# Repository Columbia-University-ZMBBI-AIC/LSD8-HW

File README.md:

# LSD8-HW
LED Synchronous Driver Hardware

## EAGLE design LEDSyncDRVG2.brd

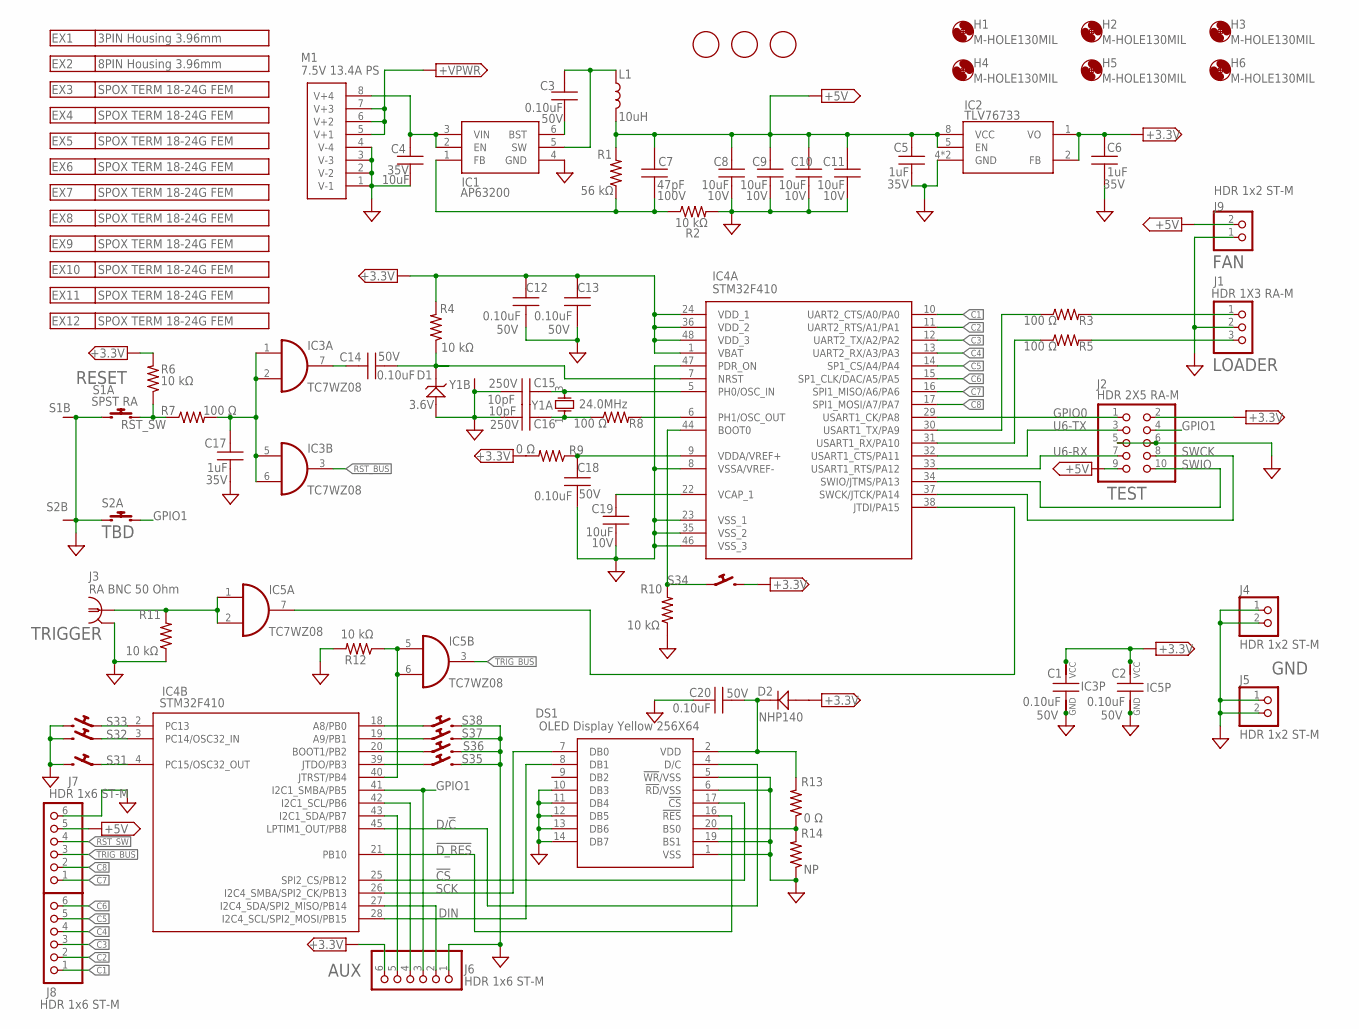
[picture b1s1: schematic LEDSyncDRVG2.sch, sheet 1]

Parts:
C1, C2, C3, C12, C13, C14, C18, C20: 0.10uF; MLCC_0603
C4: 10uF; MLCC_1206
C5, C6, C17: 1uF; MLCC_0603
C7: 47pF; MLCC_0603
C8, C9, C10, C11, C19: 10uF; MLCC_0603
C15, C16: 10pF; MLCC_0603
D1: 3.6V; SOD3716X135N_DIODE
D2: NHP140; SOD-123FL
DS1: OLED Display Yellow 256X64; DISPLAY20P
H1, H2, H3, H4, H5, H6: M-HOLE130MIL; 4-40_130HOLE_260CLEAR
IC1: AP63200; SOT95P280X100-6N
IC2: TLV76733; VSSOP8-DGK-065P
IC3, IC5: TC7WZ08; SOP50P310X90-8N
IC4: STM32F410; QFP50P900X900X160-48N
J1: HDR 1X3 RA-M; HDR_1X3RAS
J2: HDR 2X5 RA-M; HDR_2X5M_RAS
J3: RA BNC 50 Ohm; BNC_AMP_227161
J4, J5, J9: HDR 1x2 ST-M; HDR_1X2
J6: HDR 1x6 ST-M; HDR_1X06
J7, J8: HDR 1x6 ST-M; HDR_1X06; MPN NP
L1: 10uH; IND_5X5MM-5045
M1: 7.5V 13.4A PS; PS_5X3_MOLEX8P
R1: 56 kΩ; R0603
R2, R4, R6, R10, R11, R12: 10 kΩ; R0603
R3, R5, R7, R8: 100 Ω; R0603
R9, R13: 0 Ω; R0603
R14: NP; R0603
S1, S2: SPST RA; SITCH_PB_RA_800SP9B6M6RE
S3: DIP8-RA; SWITCHX8_DIP_RA_0.1IN
U$1, U$2, U$3: FIDUCIAL; FIDUCIAL_1MM
Y1: 24.0MHz; XTAL4P_3.2X2.5MM

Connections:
!CS: DS1.17 (!CS), IC4.25 (SPI2_CS/PB12)
!D_RES: DS1.16 (!RES), IC4.21 (PB10)
+3.3V: C1.2, C2.2, C6.1, C12.2, C13.2, D2.2 (A), IC2.1 (VO), IC2.2 (FB), IC3.8 (VCC), IC4.1 (VBAT), IC4.24 (VDD_1), IC4.36 (VDD_2), IC4.48 (VDD_3), IC5.8 (VCC), J2.2, J6.6, R4.2, R6.2, R9.2, S3.8; also elsewhere on the board
+5V: C5.1, C7.2, C8.2, C9.2, C10.2, C11.2, IC2.5 (EN), IC2.8 (VCC), J2.9, J7.5, J9.2, L1.2, R1.2; also elsewhere on the board
+VPWR: M1.5 (V+1), M1.6 (V+2), M1.7 (V+3); also elsewhere on the board
C1: IC4.10 (UART2_CTS/A0/PA0), J8.1; also elsewhere on the board
C2: IC4.11 (UART2_RTS/A1/PA1), J8.2; also elsewhere on the board
C3: IC4.12 (UART2_TX/A2/PA2), J8.3; also elsewhere on the board
C4: IC4.13 (UART2_RX/A3/PA3), J8.4; also elsewhere on the board
C5: IC4.14 (SP1_CS/A4/PA4), J8.5; also elsewhere on the board
C6: IC4.15 (SP1_CLK/DAC/A5/PA5), J8.6; also elsewhere on the board
C7: IC4.16 (SPI1_MISO/A6/PA6), J7.1; also elsewhere on the board
C8: IC4.17 (SPI1_MOSI/A7/PA7), J7.2; also elsewhere on the board
D/!C: DS1.4 (D/C), IC4.45 (LPTIM1_OUT/PB8)
DIN: DS1.8 (DB1), IC4.28 (I2C4_SCL/SPI2_MOSI/PB15)
GND: C1.1, C2.1, C4.2, C5.2, C6.2, C8.1, C9.1, C10.1, C11.1, C12.1, C13.1, C15.1, C16.1, C17.2, C18.1, C19.1, C20.2, D1.2 (A), DS1.1 (VSS), DS1.5 (!WR!/VSS), DS1.6 (!RD!/VSS), DS1.10 (DB3), DS1.11 (DB4), DS1.12 (DB5), DS1.13 (DB6), DS1.14 (DB7), DS1.19 (BS1), IC1.4 (GND), IC2.4 (GND), IC2.6 (GND), IC3.4 (GND), IC4.8 (VSSA/VREF-), IC4.23 (VSS_1), IC4.35 (VSS_2), IC4.46 (VSS_3), IC4.47 (PDR_ON), IC5.4 (GND), J1.2, J2.5, J2.6, J3.2, J4.1, J4.2, J5.1, J5.2, J6.1, J7.6, J9.1, M1.1 (V-1), M1.2 (V-2), M1.3 (V-3), M1.4 (V-4), R2.2, R10.1, R11.1, R12.2, R14.1, S1.1, S1.MH1 (G1), S1.MH2 (G1), S2.1, S2.MH1 (G1), S2.MH2 (G1), S3.2, S3.4, S3.6, S3.10, S3.12, S3.14, S3.16, Y1.2 (G1), Y1.4 (G1); also elsewhere on the board
GPIO0: IC4.29 (USART1_CK/PA8), J2.1
GPIO1: IC4.41 (I2C1_SMBA/PB5), J2.4, J6.3, S2.3
unnamed: C4.1, IC1.2 (EN), IC1.3 (VIN), M1.8 (V+4)
unnamed: IC4.6 (PH1/OSC_OUT), R8.2
unnamed: C16.2, R8.1, Y1.1 (IO)
unnamed: C15.2, IC4.5 (PH0/OSC_IN), Y1.3 (OI)
unnamed: C18.2, IC4.9 (VDDA/VREF+), R9.1
unnamed: IC4.3 (PC14/OSC32_IN), S3.3
unnamed: C19.2, IC4.22 (VCAP_1)
unnamed: IC4.44 (BOOT0), R10.2, S3.7
unnamed: C14.1, D1.1 (K), IC4.7 (NRST), R4.1
unnamed: C3.2, IC1.5 (SW), L1.1
unnamed: C7.1, IC1.1 (FB), R1.1, R2.1
unnamed: C3.1, IC1.6 (BST)
unnamed: IC4.18 (A8/PB0), S3.15
unnamed: IC4.19 (A9/PB1), S3.13
unnamed: J1.3, R5.2
unnamed: J1.1, R3.2
unnamed: IC4.20 (BOOT1/PB2), S3.11
unnamed: IC4.39 (JTDO/PB3), S3.9
unnamed: IC4.2 (PC13), S3.5
unnamed: DS1.20 (BS0), R13.1, R14.2
unnamed: IC4.4 (PC15/OSC32_OUT), S3.1
unnamed: IC4.38 (JTDI/PA15), IC5.7 (O)
unnamed: C20.1, D2.1 (K), DS1.2 (VDD), R13.2
unnamed: IC4.27 (I2C4_SDA/SPI2_MISO/PB14), J6.2
unnamed: IC4.30 (USART1_TX/PA9), R3.1
unnamed: IC4.43 (I2C1_SDA/PB7), J6.5
unnamed: IC4.42 (I2C1_SCL/PB6), J6.4
unnamed: C14.2, IC3.7 (O)
unnamed: IC4.31 (USART1_RX/PA10), R5.1
unnamed: IC4.40 (JTRST/PB4), IC5.5 (I0), IC5.6 (I1), R12.1
unnamed: IC5.1 (I0), IC5.2 (I1), J3.1, R11.2
RST: C17.1, IC3.1 (I0), IC3.2 (I1), IC3.5 (I0), IC3.6 (I1), R7.2
RST_BUS: IC3.3 (O); also elsewhere on the board
RST_SW: J7.4, R6.1, R7.1, S1.3
SCK: DS1.7 (DB0), IC4.26 (I2C4_SMBA/SPI2_CK/PB13)
SWCK: IC4.37 (SWCK/JTCK/PA14), J2.8
SWIO: IC4.34 (SWIO/JTMS/PA13), J2.10
TRIG_BUS: IC5.3 (O), J7.3; also elsewhere on the board
U6-RX: IC4.33 (USART1_RTS/PA12), J2.7
U6-TX: IC4.32 (USART1_CTS/PA11), J2.3

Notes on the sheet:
TEST
AUX
LOADER
TRIGGER
GND
RESET
TBD
FAN

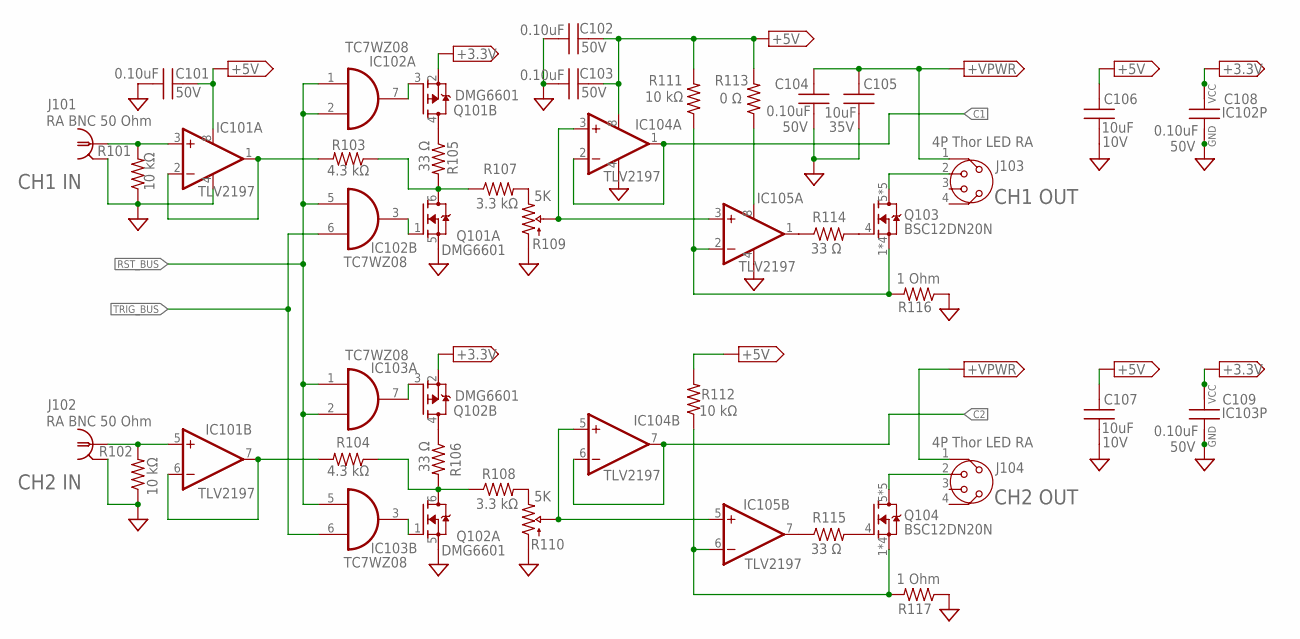
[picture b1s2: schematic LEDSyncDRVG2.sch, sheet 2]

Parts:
C101, C102, C103, C104, C108, C109: 0.10uF; MLCC_0603
C105: 10uF; MLCC_1206
C106, C107: 10uF; MLCC_0603
IC101, IC104, IC105: TLV2197; VSSOP8-DGK-065P
IC102, IC103: TC7WZ08; SOP50P310X90-8N
J101, J102: RA BNC 50 Ohm; BNC_AMP_227161
J103, J104: 4P Thor LED RA; CIR_PHX4P_RA
Q101, Q102: DMG6601; SOT95P280X100-6N
Q103, Q104: BSC12DN20N; TDSON-8
R101, R102, R111, R112: 10 kΩ; R0603
R103, R104: 4.3 kΩ; R0603
R105, R106, R114, R115: 33 Ω; R0603
R107, R108: 3.3 kΩ; R0603
R109, R110: 5K; MTBOURNS_RA_LONG
R113: 0 Ω; R0603
R116, R117: 1 Ohm; R1225

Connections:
+3.3V: C108.2, C109.2, IC102.8 (VCC), IC103.8 (VCC), Q101.2 (S), Q102.2 (S); also elsewhere on the board
+5V: C101.2, C102.2, C103.2, C106.2, C107.2, IC101.8 (V+), IC104.8 (V+), R111.2, R112.2, R113.2; also elsewhere on the board
+VPWR: C104.2, C105.1, J103.1, J104.1; also elsewhere on the board
C1: IC104.1 (OUT), IC104.2 (-IN); also elsewhere on the board
C2: IC104.6 (-IN), IC104.7 (OUT); also elsewhere on the board
GND: C101.1, C102.1, C103.1, C104.1, C105.2, C106.1, C107.1, C108.1, C109.1, IC101.4 (V-), IC102.4 (GND), IC103.4 (GND), IC104.4 (V-), IC105.4 (V-), J101.2, J102.2, Q101.5 (S), Q102.5 (S), R101.1, R102.1, R109.1 (START), R110.1 (START), R116.1, R117.1; also elsewhere on the board
unnamed: Q102.4 (D), R106.1
unnamed: Q101.4 (D), R105.1
unnamed: Q101.6 (D), R103.1, R105.2, R107.1
unnamed: IC102.3 (O), Q101.1 (G)
unnamed: IC102.7 (O), Q101.3 (G)
unnamed: IC101.1 (OUT), IC101.2 (-IN), R103.2
unnamed: IC101.3 (+IN), J101.1, R101.2
unnamed: R107.2, R109.3 (END)
unnamed: Q102.6 (D), R104.1, R106.2, R108.1
unnamed: IC104.3 (+IN), IC105.3 (+IN), R109.2 (WIPER)
unnamed: IC105.1 (OUT), R114.1
unnamed: IC105.2 (-IN), Q103.1 (S), Q103.2 (S), Q103.3 (S), Q103.10 (S), R111.1, R116.2
unnamed: Q103.4 (G), R114.2
unnamed: IC103.3 (O), Q102.1 (G)
unnamed: J103.2, Q103.5 (D), Q103.6 (D), Q103.7 (D), Q103.8 (D), Q103.9 (D)
unnamed: IC103.7 (O), Q102.3 (G)
unnamed: IC101.5 (+IN), J102.1, R102.2
unnamed: IC101.6 (-IN), IC101.7 (OUT), R104.2
unnamed: R108.2, R110.3 (END)
unnamed: IC104.5 (+IN), IC105.5 (+IN), R110.2 (WIPER)
unnamed: IC105.6 (-IN), Q104.1 (S), Q104.2 (S), Q104.3 (S), Q104.10 (S), R112.1, R117.2
unnamed: IC105.7 (OUT), R115.1
unnamed: Q104.4 (G), R115.2
unnamed: J104.2, Q104.5 (D), Q104.6 (D), Q104.7 (D), Q104.8 (D), Q104.9 (D)
unnamed: IC105.8 (V+), R113.1
RST_BUS: IC102.1 (I0), IC102.2 (I1), IC102.5 (I0), IC103.1 (I0), IC103.2 (I1), IC103.5 (I0); also elsewhere on the board
TRIG_BUS: IC102.6 (I1), IC103.6 (I1); also elsewhere on the board

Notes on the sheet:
CH1 IN
CH2 IN
CH1 OUT
CH2 OUT

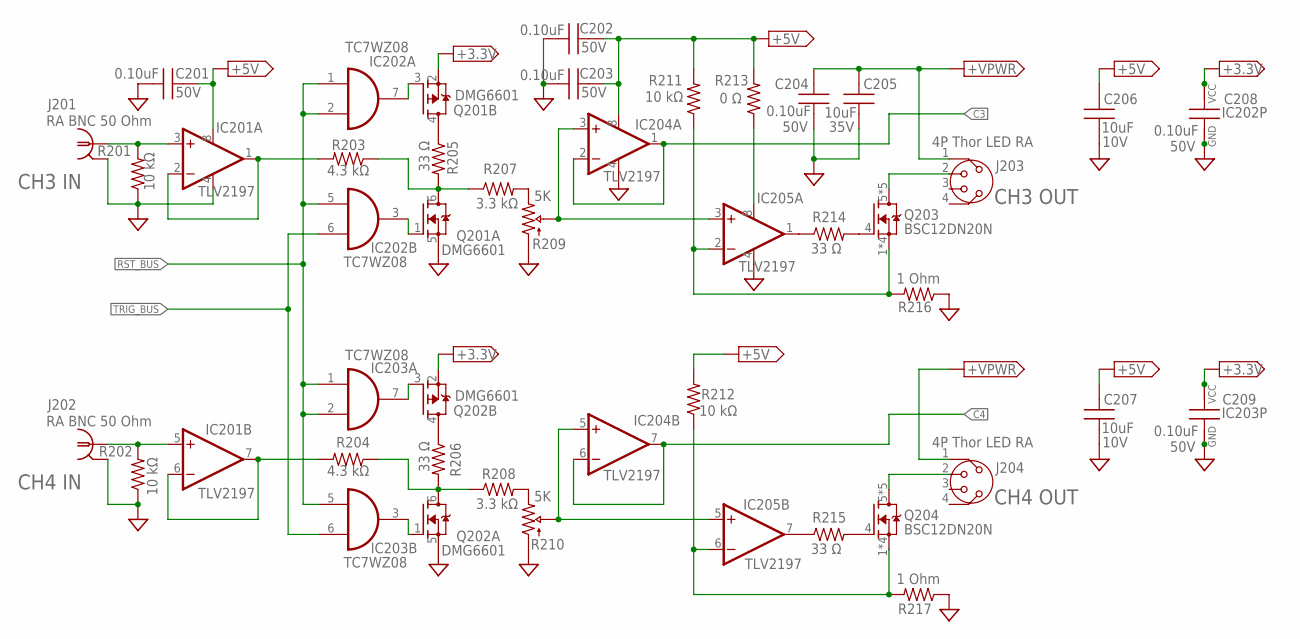
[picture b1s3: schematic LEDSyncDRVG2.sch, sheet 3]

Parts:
C201, C202, C203, C204, C208, C209: 0.10uF; MLCC_0603
C205: 10uF; MLCC_1206
C206, C207: 10uF; MLCC_0603
IC201, IC204, IC205: TLV2197; VSSOP8-DGK-065P
IC202, IC203: TC7WZ08; SOP50P310X90-8N
J201, J202: RA BNC 50 Ohm; BNC_AMP_227161
J203, J204: 4P Thor LED RA; CIR_PHX4P_RA
Q201, Q202: DMG6601; SOT95P280X100-6N
Q203, Q204: BSC12DN20N; TDSON-8
R201, R202, R211, R212: 10 kΩ; R0603
R203, R204: 4.3 kΩ; R0603
R205, R206, R214, R215: 33 Ω; R0603
R207, R208: 3.3 kΩ; R0603
R209, R210: 5K; MTBOURNS_RA_LONG
R213: 0 Ω; R0603
R216, R217: 1 Ohm; R1225

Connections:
+3.3V: C208.2, C209.2, IC202.8 (VCC), IC203.8 (VCC), Q201.2 (S), Q202.2 (S); also elsewhere on the board
+5V: C201.2, C202.2, C203.2, C206.2, C207.2, IC201.8 (V+), IC204.8 (V+), R211.2, R212.2, R213.2; also elsewhere on the board
+VPWR: C204.2, C205.1, J203.1, J204.1; also elsewhere on the board
C3: IC204.1 (OUT), IC204.2 (-IN); also elsewhere on the board
C4: IC204.6 (-IN), IC204.7 (OUT); also elsewhere on the board
GND: C201.1, C202.1, C203.1, C204.1, C205.2, C206.1, C207.1, C208.1, C209.1, IC201.4 (V-), IC202.4 (GND), IC203.4 (GND), IC204.4 (V-), IC205.4 (V-), J201.2, J202.2, Q201.5 (S), Q202.5 (S), R201.1, R202.1, R209.1 (START), R210.1 (START), R216.1, R217.1; also elsewhere on the board
unnamed: Q201.4 (D), R205.1
unnamed: Q201.6 (D), R203.1, R205.2, R207.1
unnamed: IC202.3 (O), Q201.1 (G)
unnamed: IC202.7 (O), Q201.3 (G)
unnamed: IC201.3 (+IN), J201.1, R201.2
unnamed: IC201.1 (OUT), IC201.2 (-IN), R203.2
unnamed: R207.2, R209.3 (END)
unnamed: IC204.3 (+IN), IC205.3 (+IN), R209.2 (WIPER)
unnamed: IC205.2 (-IN), Q203.1 (S), Q203.2 (S), Q203.3 (S), Q203.10 (S), R211.1, R216.2
unnamed: IC205.1 (OUT), R214.1
unnamed: Q203.4 (G), R214.2
unnamed: J203.2, Q203.5 (D), Q203.6 (D), Q203.7 (D), Q203.8 (D), Q203.9 (D)
unnamed: Q202.4 (D), R206.1
unnamed: Q202.6 (D), R204.1, R206.2, R208.1
unnamed: IC203.3 (O), Q202.1 (G)
unnamed: IC203.7 (O), Q202.3 (G)
unnamed: IC201.5 (+IN), J202.1, R202.2
unnamed: IC201.6 (-IN), IC201.7 (OUT), R204.2
unnamed: R208.2, R210.3 (END)
unnamed: IC204.5 (+IN), IC205.5 (+IN), R210.2 (WIPER)
unnamed: IC205.6 (-IN), Q204.1 (S), Q204.2 (S), Q204.3 (S), Q204.10 (S), R212.1, R217.2
unnamed: Q204.4 (G), R215.2
unnamed: J204.2, Q204.5 (D), Q204.6 (D), Q204.7 (D), Q204.8 (D), Q204.9 (D)
unnamed: IC205.7 (OUT), R215.1
unnamed: IC205.8 (V+), R213.1
RST_BUS: IC202.1 (I0), IC202.2 (I1), IC202.5 (I0), IC203.1 (I0), IC203.2 (I1), IC203.5 (I0); also elsewhere on the board
TRIG_BUS: IC202.6 (I1), IC203.6 (I1); also elsewhere on the board

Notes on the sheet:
CH3 IN
CH4 IN
CH3 OUT
CH4 OUT

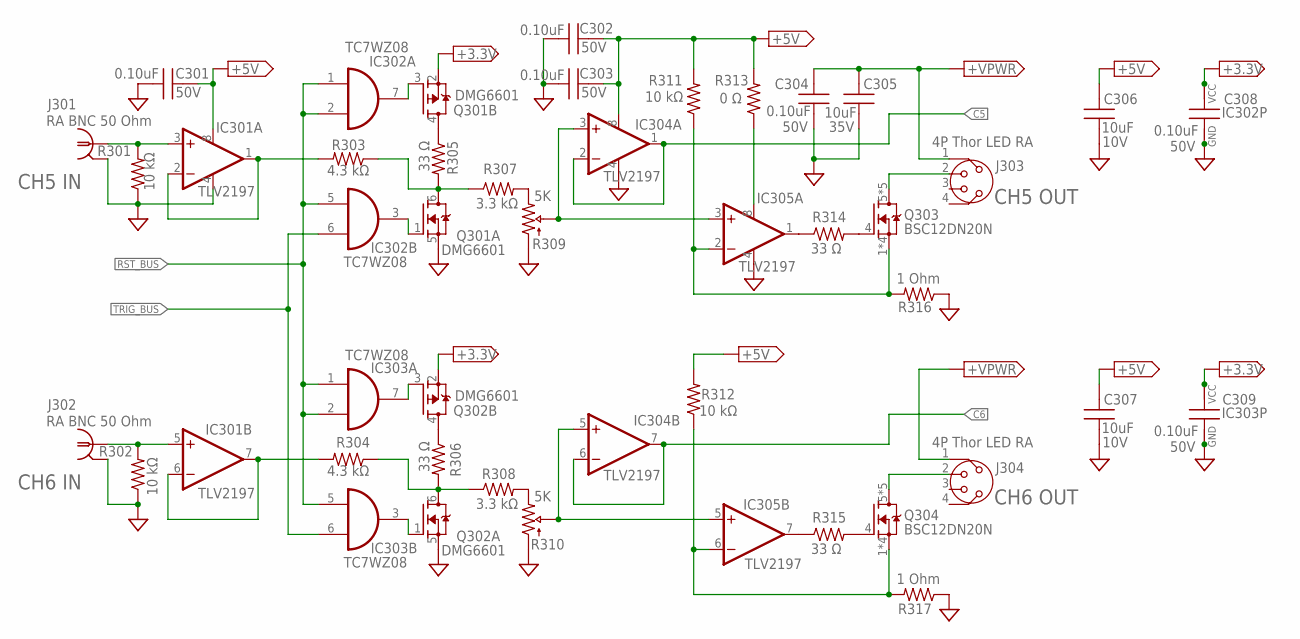
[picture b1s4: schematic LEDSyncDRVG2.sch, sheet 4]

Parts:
C301, C302, C303, C304, C308, C309: 0.10uF; MLCC_0603
C305: 10uF; MLCC_1206
C306, C307: 10uF; MLCC_0603
IC301, IC304, IC305: TLV2197; VSSOP8-DGK-065P
IC302, IC303: TC7WZ08; SOP50P310X90-8N
J301, J302: RA BNC 50 Ohm; BNC_AMP_227161
J303, J304: 4P Thor LED RA; CIR_PHX4P_RA
Q301, Q302: DMG6601; SOT95P280X100-6N
Q303, Q304: BSC12DN20N; TDSON-8
R301, R302, R311, R312: 10 kΩ; R0603
R303, R304: 4.3 kΩ; R0603
R305, R306, R314, R315: 33 Ω; R0603
R307, R308: 3.3 kΩ; R0603
R309, R310: 5K; MTBOURNS_RA_LONG
R313: 0 Ω; R0603
R316, R317: 1 Ohm; R1225

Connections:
+3.3V: C308.2, C309.2, IC302.8 (VCC), IC303.8 (VCC), Q301.2 (S), Q302.2 (S); also elsewhere on the board
+5V: C301.2, C302.2, C303.2, C306.2, C307.2, IC301.8 (V+), IC304.8 (V+), R311.2, R312.2, R313.2; also elsewhere on the board
+VPWR: C304.2, C305.1, J303.1, J304.1; also elsewhere on the board
C5: IC304.1 (OUT), IC304.2 (-IN); also elsewhere on the board
C6: IC304.6 (-IN), IC304.7 (OUT); also elsewhere on the board
GND: C301.1, C302.1, C303.1, C304.1, C305.2, C306.1, C307.1, C308.1, C309.1, IC301.4 (V-), IC302.4 (GND), IC303.4 (GND), IC304.4 (V-), IC305.4 (V-), J301.2, J302.2, Q301.5 (S), Q302.5 (S), R301.1, R302.1, R309.1 (START), R310.1 (START), R316.1, R317.1; also elsewhere on the board
unnamed: Q301.4 (D), R305.1
unnamed: Q301.6 (D), R303.1, R305.2, R307.1
unnamed: IC302.3 (O), Q301.1 (G)
unnamed: IC302.7 (O), Q301.3 (G)
unnamed: IC301.3 (+IN), J301.1, R301.2
unnamed: IC301.1 (OUT), IC301.2 (-IN), R303.2
unnamed: R307.2, R309.3 (END)
unnamed: IC304.3 (+IN), IC305.3 (+IN), R309.2 (WIPER)
unnamed: IC305.2 (-IN), Q303.1 (S), Q303.2 (S), Q303.3 (S), Q303.10 (S), R311.1, R316.2
unnamed: IC305.1 (OUT), R314.1
unnamed: Q303.4 (G), R314.2
unnamed: J303.2, Q303.5 (D), Q303.6 (D), Q303.7 (D), Q303.8 (D), Q303.9 (D)
unnamed: Q302.4 (D), R306.1
unnamed: Q302.6 (D), R304.1, R306.2, R308.1
unnamed: IC303.3 (O), Q302.1 (G)
unnamed: IC303.7 (O), Q302.3 (G)
unnamed: IC301.5 (+IN), J302.1, R302.2
unnamed: IC301.6 (-IN), IC301.7 (OUT), R304.2
unnamed: R308.2, R310.3 (END)
unnamed: IC304.5 (+IN), IC305.5 (+IN), R310.2 (WIPER)
unnamed: IC305.6 (-IN), Q304.1 (S), Q304.2 (S), Q304.3 (S), Q304.10 (S), R312.1, R317.2
unnamed: Q304.4 (G), R315.2
unnamed: J304.2, Q304.5 (D), Q304.6 (D), Q304.7 (D), Q304.8 (D), Q304.9 (D)
unnamed: IC305.7 (OUT), R315.1
unnamed: IC305.8 (V+), R313.1
RST_BUS: IC302.1 (I0), IC302.2 (I1), IC302.5 (I0), IC303.1 (I0), IC303.2 (I1), IC303.5 (I0); also elsewhere on the board
TRIG_BUS: IC302.6 (I1), IC303.6 (I1); also elsewhere on the board

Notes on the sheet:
CH5 IN
CH6 IN
CH5 OUT
CH6 OUT

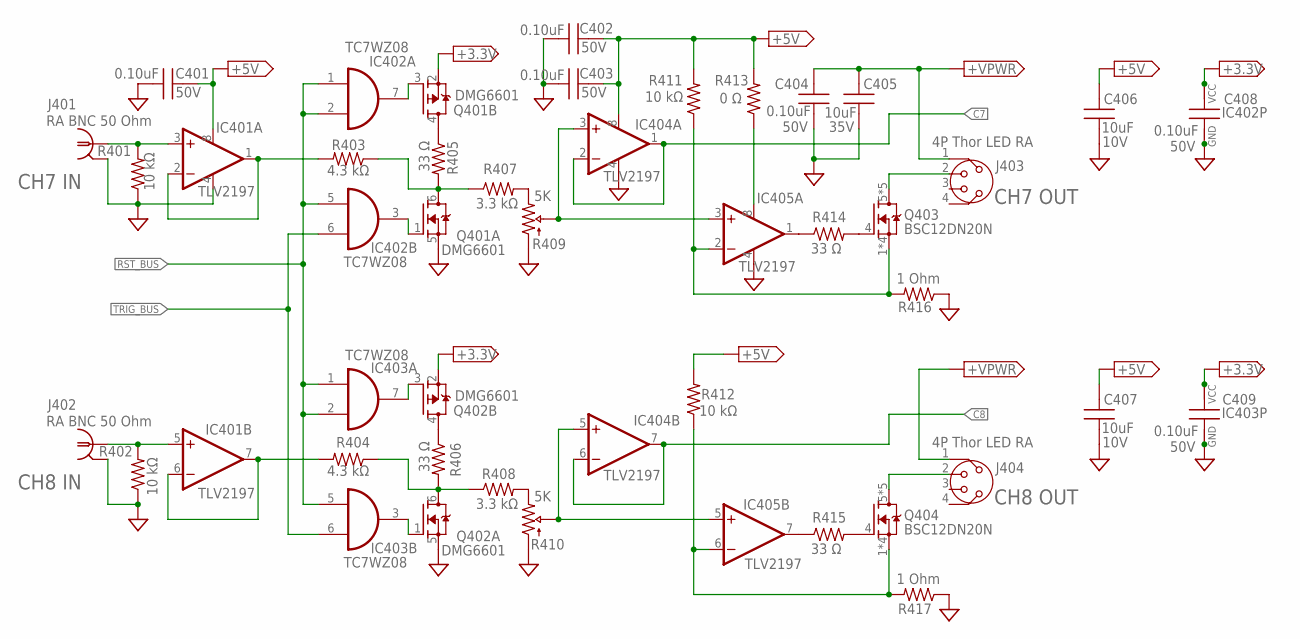
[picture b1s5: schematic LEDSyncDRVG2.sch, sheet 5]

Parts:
C401, C402, C403, C404, C408, C409: 0.10uF; MLCC_0603
C405: 10uF; MLCC_1206
C406, C407: 10uF; MLCC_0603
IC401, IC404, IC405: TLV2197; VSSOP8-DGK-065P
IC402, IC403: TC7WZ08; SOP50P310X90-8N
J401, J402: RA BNC 50 Ohm; BNC_AMP_227161
J403, J404: 4P Thor LED RA; CIR_PHX4P_RA
Q401, Q402: DMG6601; SOT95P280X100-6N
Q403, Q404: BSC12DN20N; TDSON-8
R401, R402, R411, R412: 10 kΩ; R0603
R403, R404: 4.3 kΩ; R0603
R405, R406, R414, R415: 33 Ω; R0603
R407, R408: 3.3 kΩ; R0603
R409, R410: 5K; MTBOURNS_RA_LONG
R413: 0 Ω; R0603
R416, R417: 1 Ohm; R1225

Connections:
+3.3V: C408.2, C409.2, IC402.8 (VCC), IC403.8 (VCC), Q401.2 (S), Q402.2 (S); also elsewhere on the board
+5V: C401.2, C402.2, C403.2, C406.2, C407.2, IC401.8 (V+), IC404.8 (V+), R411.2, R412.2, R413.2; also elsewhere on the board
+VPWR: C404.2, C405.1, J403.1, J404.1; also elsewhere on the board
C7: IC404.1 (OUT), IC404.2 (-IN); also elsewhere on the board
C8: IC404.6 (-IN), IC404.7 (OUT); also elsewhere on the board
GND: C401.1, C402.1, C403.1, C404.1, C405.2, C406.1, C407.1, C408.1, C409.1, IC401.4 (V-), IC402.4 (GND), IC403.4 (GND), IC404.4 (V-), IC405.4 (V-), J401.2, J402.2, Q401.5 (S), Q402.5 (S), R401.1, R402.1, R409.1 (START), R410.1 (START), R416.1, R417.1; also elsewhere on the board
unnamed: Q401.4 (D), R405.1
unnamed: Q401.6 (D), R403.1, R405.2, R407.1
unnamed: IC402.3 (O), Q401.1 (G)
unnamed: IC402.7 (O), Q401.3 (G)
unnamed: IC401.3 (+IN), J401.1, R401.2
unnamed: IC401.1 (OUT), IC401.2 (-IN), R403.2
unnamed: R407.2, R409.3 (END)
unnamed: IC404.3 (+IN), IC405.3 (+IN), R409.2 (WIPER)
unnamed: IC405.2 (-IN), Q403.1 (S), Q403.2 (S), Q403.3 (S), Q403.10 (S), R411.1, R416.2
unnamed: IC405.1 (OUT), R414.1
unnamed: Q403.4 (G), R414.2
unnamed: J403.2, Q403.5 (D), Q403.6 (D), Q403.7 (D), Q403.8 (D), Q403.9 (D)
unnamed: Q402.4 (D), R406.1
unnamed: Q402.6 (D), R404.1, R406.2, R408.1
unnamed: IC403.3 (O), Q402.1 (G)
unnamed: IC403.7 (O), Q402.3 (G)
unnamed: IC401.5 (+IN), J402.1, R402.2
unnamed: IC401.6 (-IN), IC401.7 (OUT), R404.2
unnamed: R408.2, R410.3 (END)
unnamed: IC404.5 (+IN), IC405.5 (+IN), R410.2 (WIPER)
unnamed: IC405.6 (-IN), Q404.1 (S), Q404.2 (S), Q404.3 (S), Q404.10 (S), R412.1, R417.2
unnamed: Q404.4 (G), R415.2
unnamed: J404.2, Q404.5 (D), Q404.6 (D), Q404.7 (D), Q404.8 (D), Q404.9 (D)
unnamed: IC405.7 (OUT), R415.1
unnamed: IC405.8 (V+), R413.1
RST_BUS: IC402.1 (I0), IC402.2 (I1), IC402.5 (I0), IC403.1 (I0), IC403.2 (I1), IC403.5 (I0); also elsewhere on the board
TRIG_BUS: IC402.6 (I1), IC403.6 (I1); also elsewhere on the board

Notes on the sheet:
CH7 IN
CH8 IN
CH7 OUT
CH8 OUT

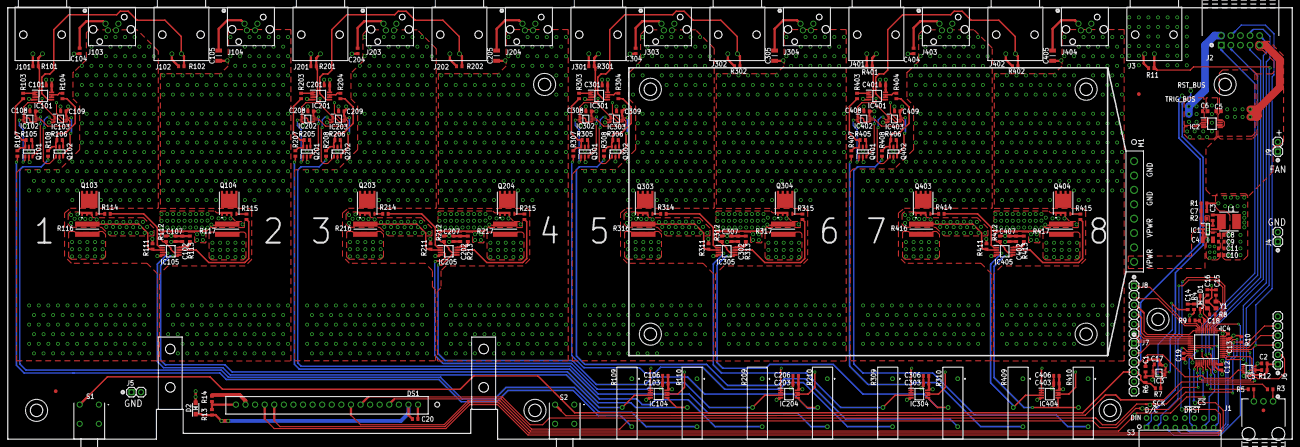
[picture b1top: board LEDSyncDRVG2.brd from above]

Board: 4 copper layers, 340.4 x 114.3 mm, 222 parts (0 on the bottom side), 158 nets.

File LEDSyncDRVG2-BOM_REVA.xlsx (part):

| REVA | LED Sync. Driver 8 Channels GEN2 |  | 44235
Qty | MPN | MNF | Parts | VALUE | DESCRIPTION | Package | CURRENT | POWER | TOLERANCE | VOLTAGE | VENDOR | Notes | DATASHEET
32 | 06035C104JAT2A | AVX | C1, C2, C3, C12, C13, C14, C18, C20, C101, C102, C103, C104, C108, C109, C201, 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 | 0.10uF | Multilayer Ceramic Capacitor (MLCC)X7R 0603, 0.10uF 5%, 50V | MLCC_0603 |  |  | 0.05 | 50V | Mouser |  | https://www.mouser.com/datasheet/2/40/X7RDielectric-777024.pdf
2 | VJ0603D100JXPAJ | Murata | C15, C16 | 10pF | Multilayer Ceramic Capacitor (MLCC)C0G HF 0603, 10pF 5%, 250V | MLCC_0603 |  |  | +/-0.05pF | 250V | Mouser |  | https://www.mouser.com/datasheet/2/427/vjhifreq-1391225.pdf
5 | GMK316AB7106KL-TR | TAIYO YUDEN | C4, C105, C205, C305, C405 | 10uF | Ceramic Capacitor X7R 1206 35V 10uF | MLCC_1206 |  |  |  | 35V | Mouser |  | https://componentsearchengine.com/Datasheets/1/TMK316AB7106KLHT.pdf
3 | CGA3E1X7R1V105K080AC | TDK | C5, C6, C17 | 1uF | Multilayer Ceramic Capacitor (MLCC)X7R 0603, 1uF 10%, 35V | MLCC_0603 |  |  | 0.1 | 35V | Mouser |  | https://www.mouser.com/datasheet/2/400/lcc_automotive_genera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
1 | GCM1885C2A470FA16D | Murata | C7 | 47pF | Multilayer Ceramic Capacitor (MLCC)C0G HF 0603, 47pF 1%, 100V | MLCC_0603 |  |  | 0.01 | 100V | Mouser |  | https://psearch.en.murata.com/capacitor/lineup/gcm/?excid=ww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
13 | 0603ZD106KAT2A | AVX | C8, C9, C10, C11, C19, C106, C107, C206, C207, C306, C307, C406, C407 | 10uF | Multilayer Ceramic Capacitor (MLCC)X5R 0603, 10uF 10%, 10V | MLCC_0603 |  |  | 0.1 | 10V | Mouser |  | https://www.mouser.com/datasheet/2/40/cx5r-776519.pdf
1 | MMSZ3V6T1G | ON Semi | D1 | 3.6V | ZENNER DIODE, 0.5W, 3.6V, SMT SOD123-2 | SOD3716X135N_DIODE | 100mA | 0.5W max |  |  | Mouser |  | https://www.mouser.com/datasheet/2/308/MMSZ2V4T1-D-87271.pdf
1 | NHP140SFT3G | ON Semi | D2 | NHP140 | Rectifier Diode 1A 400V. SOD−123FL | SOD-123FL | 1A | 330 degC/W |  |  | Mouser |  | https://www.onsemi.com/pub/Collateral/NHP140SF-D.PDF.pdf
1 | AP63200WU-7 | Diodes Inc. | IC1 | AP63200 | Switching Voltage Regulators DCDC Conv HV Buck TSOT26 | SOT95P280X100-6N |  |  |  |  | Mouser
12 | TLV2197QDGKRQ1 | Texas Instruments | IC101, IC104, IC105, IC201, IC204, IC205, IC301, IC304, IC305, IC401, IC404, IC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 | TLV2197 | 36-V, Single-Supply, 10-MHz, Rail-to-Rail IN&Output, Dual Operational Amplifier | VSSOP8-DGK-065P |  |  |  |  | Mouser |  | https://www.ti.com/lit/ds/symlink/tlv197-q1.pdf?ts=159548343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
1 | TLV76733DGNR | TI | IC2 | TLV76733 | Precision Linear Voltage Regulator FIX 3.3V 1A 16V max in Drop 1.5V VSSOP PAD | VSSOP8-DGK-065P |  |  |  |  | Mouser |  | https://www.ti.com/lit/ds/symlink/tlv767.pdf?ts=161230989378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
10 | TC7WZ08FK | Toshiba | IC3, IC5, IC102, IC103, IC202, IC203, IC302, IC303, IC402, IC403 | TC7WZ08 | Logic Gates Dual AND in TSSOP | SOP50P310X90-8N |  |  |  |  | Mouser |  | https://toshiba.semicon-storage.com/info/docget.jsp?did=5467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
1 | STM32F410CBT3 | STMicroelectronics | IC4 | STM32F410 | MCU STM32F410 Cortex M4 125DMips 128KBFlash, 32KB Ram, ADC/DAC, LQFP48 | QFP50P900X900X160-48N |  |  |  |  | Mouser |  | https://www.mouser.com/datasheet/2/389/stm32f410cb-1851313.pdf
1 | VLS5045EX-100M | TDK | L1 | 10uH | TDK VLS-EX Series Type 5045 Shielded Wire-wound SMD Inductor with a Ferrite Cor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 | IND_5X5MM-5045 |  |  |  |  | Mouser |  | https://componentsearchengine.com/Datasheets/1/VLS5045EX-100M.pdf
1 | CFM100M075 | Cincon | M1 | 7.5V 13.4A PS | OPEN FRAME 3X5 AC-DC PS MODULE WITH PFC ,100W MEDICAL&ITE, 7.5V 13.4A" | PS_5X3_MOLEX8P |  |  |  |  | Mouser |  | https://www.cincon.com/productdownload/SPEC-CFM100M-V19.pdf
8 | DMG6601LVT-7 | Diodes | Q101, Q102, Q201, Q202, Q301, Q302, Q401, Q402 | DMG6601 | Diodes Inc DMG6601LVT-7 Dual N/P-channel MOSFET, 2 A, 3A, 30 V, 6-Pin TSOT-26 | SOT95P280X100-6N |  |  |  |  | Mouser |  | https://www.diodes.com/assets/Datasheets/DMG6601LVT.pdf
8 | BSC12DN20NS3 G | Infineon | Q103, Q104, Q203, Q204, Q303, Q304, Q403, Q404 | BSC12DN20N | N CH MOSFET 200V, 11.3A, 125mOhm ON, 12S gfs, SMT TDSON-8 | TDSON-8 | 11.3A | 50W |  |  | Mouser |  | https://www.mouser.com/datasheet/2/196/BSC12DN20NS3%20Rev2.2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
1 | CRCW060356K0FKEA | Vishay | R1 | 56 kΩ | Thick Film Resistor 0603, 56 kΩ ,1%, 0.1W | R0603 |  | 0.1W | 0.01 |  | Mouser |  | http://www.vishay.com/docs/20035/dcrcwe3.pdf
8 | CRCW06034K30FKEA | Vishay | R103, R104, R203, R204, R303, R304, R403, R404 | 4.3 kΩ | Thick Film Resistor 0603, 4.3 kΩ ,1%, 0.1W | R0603 |  | 0.1W | 0.01 |  | Mouser |  | http://www.vishay.com/docs/20035/dcrcwe3.pdf
16 | CRCW060333R0FKEA | Vishay | R105, R106, R114, R115, R205, R206, R214, R215, R305, R306, R314, R315, R405, R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 | 33 Ω | Thick Film Resistor 0603, 33 Ω ,1%, 0.1W | R0603 |  | 0.1W | 0.01 |  | Mouser |  | http://www.vishay.com/docs/20035/dcrcwe3.pdf
8 | CRCW06033K30FKEA | Vishay | R107, R108, R207, R208, R307, R308, R407, R408 | 3.3 kΩ | Thick Film Resistor 0603, 3.3 kΩ ,1%, 0.1W | R0603 |  | 0.1W | 0.01 |  | Mouser |  | http://www.vishay.com/docs/20035/dcrcwe3.pdf
8 | 3006P-7-502LF | Bourns | R109, R110, R209, R210, R309, R310, R409, R410 | 5K | Multi Turn Resistor Long, Through Hole RA 5K 10% 3/4 " | MTBOURNS_RA_LONG |  |  |  |  | Mouser |  | https://www.mouser.com/datasheet/2/54/3006-1649234.pdf
8 | WK73S3A3TTE1R00F | KOA Speer | R116, R117, R216, R217, R316, R317, R416, R417 | 1 Ohm | Thick Film Resistor Reversed 1225 1 ohm 1% 3W | R1225 |  |  |  |  | Mouser |  | https://www.mouser.com/datasheet/2/219/WK73S-1840148.pdf
22 | CRCW060310K0FKEA | Vishay | R2, R4, R6, R10, R11, R12, R101, R102, R111, R112, R201, R202, R211, R212, R301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 | 10 kΩ | Thick Film Resistor 0603, 10 kΩ ,1%, 0.1W | R0603 |  | 0.1W | 0.01 |  | Mouser |  | http://www.vishay.com/docs/20035/dcrcwe3.pdf
4 | CRCW0603100RFKEA | Vishay | R3, R5, R7, R8 | 100 Ω | Thick Film Resistor 0603, 100 Ω ,1%, 0.1W | R0603 |  | 0.1W | 0.01 |  | Mouser |  | http://www.vishay.com/docs/20035/dcrcwe3.pdf
6 | CRCW06030000Z0EA | Vishay | R9, R13, R113, R213, R313, R413 | 0 Ω | Thick Film Resistor 0603, 0 Ω ,1%, 0.1W | R0603 |  |  |  |  | Mouser |  | http://www.vishay.com/docs/20035/dcrcwe3.pdf
1 | ECS-240-8-33-RWY-TR | ECS | Y1 | 24.0MHz | Crystal 3.2X2.5mm 24MHz 15ppm 8pF -30C +55C | XTAL4P_3.2X2.5MM |  |  |  |  | Mouser |  | https://www.mouser.com/datasheet/2/122/ecx-32-1100709.pdf
1 | 800SP9B6M6RE | E-Switch | S1 | SPST RA | Pushbutton Switch SPST RA PCB With Mounting NON-THD | SITCH_PB_RA_800SP9B6M6RE |  |  |  |  | Mouser |  | https://www.mouser.com/datasheet/2/140/800-345975.pdf
1 | DS03-254-08BE | CUI | S3 | DIP8-RA | DIP Switches SPST, 2.54 pitch, Raised actuator, RA, 8 position, Blue | SWITCHX8_DIP_RA_0.1IN | 25ma |  |  | 24V | Mouser |  | https://www.mouser.com/datasheet/2/670/ds03_254-1777715.pdf
1 | 70555-0072 | Molex | J1 | HDR 1X3 RA-M | Header RA Male 1X3 Gold Shrouded 0.1 " | HDR_1X3RAS | 3A |  |  |  | Mouser |  | https://www.mouser.com/datasheet/2/276/705550071_sd-1608181.pdf
8 | 1526169 | Phoenix | J103, J104, J203, J204, J303, J304, J403, J404 | 4P Thor LED RA | Circular 4 PIN Female RA Thor Led Pinout | CIR_PHX4P_RA |  |  |  |  | Mouser |  | https://www.mouser.com/datasheet/2/324/4/1526169-1415351.pdf
1 | 30310-5002HB | 3M | J2 | HDR 2X5 RA-M | Header RA Male 2X5 Gold Shrouded 0.1 " | HDR_2X5M_RAS | 1A |  |  |  | Mouser | Molex has replacement 70247-1054 | https://www.mouser.com/datasheet/2/1/TS0818-221281.pdf
9 | 5227161-6 | TE | J3, J101, J102, J201, J202, J301, J302, J401, J402 | RA BNC 50 Ohm | BNC R.A. JACK 50 OHM ISOLATED | BNC_AMP_227161 |  |  |  |  | Mouser |  | https://www.te.com/commerce/DocumentDelivery/DDEController?A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
2 | 77311-124-02LF | Amphenol FCI | J4, J5 | HDR 1x2 ST-M | Header Straight Male 1 X 2 (2.54mm square) 6.75mm post | HDR_1X2 | 3A |  |  |  | Mouser |  | https://www.mouser.com/datasheet/2/18/77311-1266344.pdf
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
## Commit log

2022-06-30 Update LICENSE
